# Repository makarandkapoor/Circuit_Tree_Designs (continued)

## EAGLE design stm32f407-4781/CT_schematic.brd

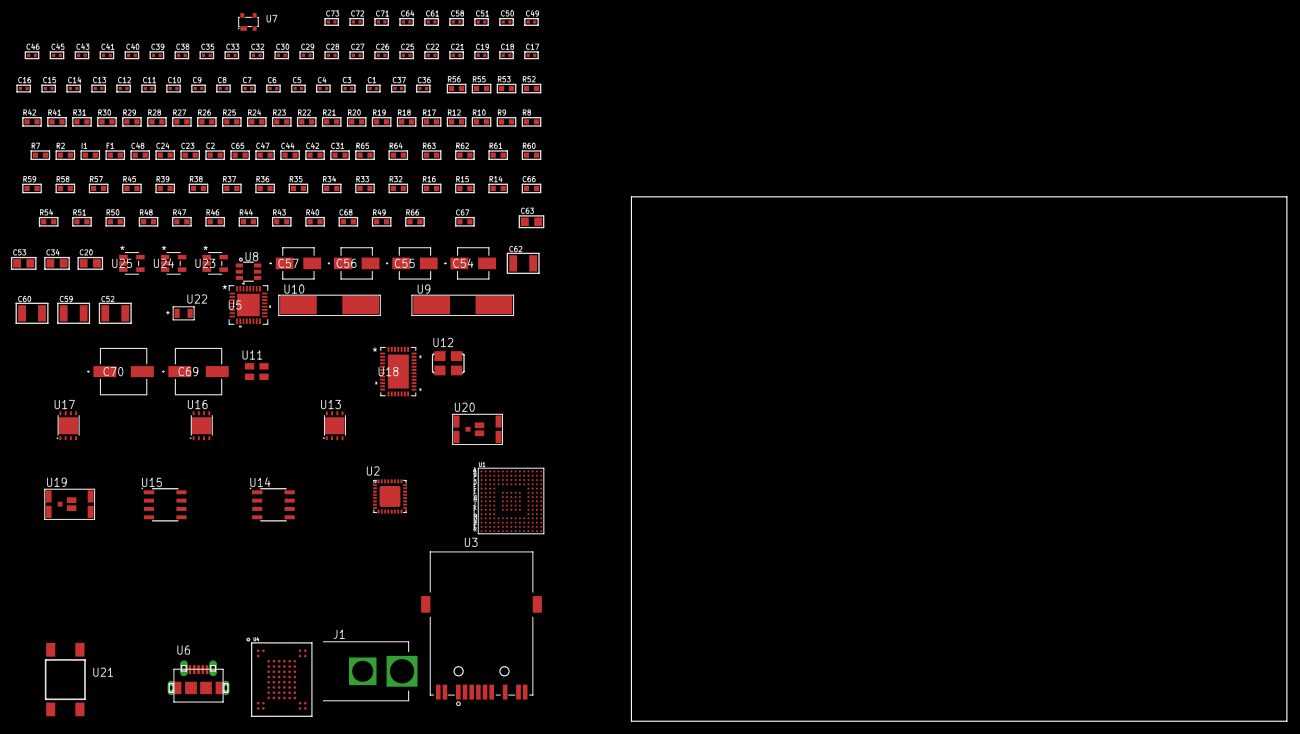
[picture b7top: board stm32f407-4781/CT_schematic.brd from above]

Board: 2 copper layers, 160 parts (0 on the bottom side), 121 nets, no tracks yet.

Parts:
C1, C3, C4, C5, C6, C7, C8, C9, C10, C11, C12, C13, C14, C15, C16, C17, C18, C19, C21, C22, C27, C28, C29, C30, C32, C33, C35, C38, C39, C40, C41, C43, C45, C46, C64: 1e-07; C0402
C2, C24, C48: 1e-06; C0603
C20: 4.7e-06; C0805
C23: 1e-08; C0603
C25, C26: 1e-11; C0402
C31, C42, C44, C47, C65: 2.2e-06; C0603
C34, C53, C63: 1e-05; C0805
C36, C37: 2.2e-11; C0402
C49, C50, C51, C58, C61, C71, C72, C73: 1e-08; C0402
C52, C59, C60, C62: 1e-05; C1210
C54, C56: 1e-06; EXV-9B
C55, C57: 2.2e-06; EXV-9B
C66: 2.45e-08; R0603
C67: 2.8258362168397e-09; R0603
C68: 7.105e-09; R0603
C69, C70: 0.0001; EXV-9H
F1: 600.0; L0603
I1: 97.0; R0603
J1: PJ-037B; PJ-037B_PACKAGE
R2, R24, R25, R26, R28, R29, R30, R42, R53, R56: 1000.0; R0603
R7, R8, R9, R22, R23, R27, R31: 4700.0; R0603
R10, R12: 2200.0; R0603
R14, R15, R16, R32, R33, R34, R35, R36, R38, R39, R57, R59, R60, R63, R64, R65: 10000.0; R0603
R17, R18: 0.1; R0603
R19, R41, R55: 200.0; R0603
R20: 220.0; R0603
R21: 6490.0; R0603
R37, R45: 47000.0; R0603
R40, R43, R44, R46, R47, R48, R50, R51, R54: 100000.0; R0603
R49: 164658.62; R0603
R52: 3900.0; R0603
R58: 75000.0; R0603
R61, R62: 95300.0; R0603
R66: 130963.63636364; R0603
U1: STM32F407IGH6; UFBGA176
U2: KSZ8081RNBIA-TR; QFN-32
U3: 7498011122R
U4: mt29f4g08abbdah4; VFBGA-63
U5: TUSB1210BRHBR; RHB32_3P45X3P45
U6: 47590-0001; MICRO_USB_AB
U7: prtr5v0u2ax; SOT143B
U8: MAX4995AAUT+T; SOT-23-6
U9, U10: ABLS-25.000MHZ-B2F-T
U11: ASEK-32.768KHz-ECST; ASEK
U12: ASFL1-19.2MHZ-NCS; ASFL1
U13, U16, U17: LP3878SDX-ADJ/NOPB; WSON-8
U14, U15: LP2954AIMX/NOPB; LP2954
U18: LTC2928CUHF#PBF; QFN-38_UHF
U19, U20: IRF8306MTRPbF; IRF8306MTRPBF
U21: 4-1437565-2; SW_4-1437565-2
U22: Q65110A2395; LGM67K-G1J2-24-Z
U23, U24, U25: nc7sz125m5x; NC7SZ125M5X

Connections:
CLK_CRYSTAL_U1_G1: C25.1, U1.G1, U9.1
CLK_CRYSTAL_U1_H1: C26.1, U1.H1, U9.2
CLK_CRYSTAL_U2_8: C36.1, U2.8, U10.2
CLK_CRYSTAL_U2_9: C37.1, U2.9, U10.1
CLK_U1_E1: U1.E1, U11.3
CLK_U5_1: U5.1, U12.3
GND: C1.2, C2.2, C3.2, C4.2, C5.2, C6.2, C7.2, C8.2, C9.2, C10.2, C11.2, C12.2, C13.2, C14.2, C15.2, C16.2, C17.2, C18.2, C19.2, C20.2, C21.2, C22.2, C23.2, C24.2, C25.2, C26.2, C27.2, C28.2, C29.2, C30.2, C31.2, C32.2, C33.2, C34.2, C35.2, C36.2, C37.2, C38.2, C39.2, C40.2, C41.2, C42.2, C43.2, C44.2, C45.2, C46.2, C47.2, C48.2, C49.2, C50.2, C51.2, C52.2, C53.2, C54.2, C55.2, C56.2, C57.2, C58.2, C59.2, C60.2, C61.2, C62.2, C63.2, C64.2, C65.2, C66.2, C67.2, C68.2, C69.2, C70.2, C71.2, C72.2, C73.2, J1.2, R2.2, R15.2, R17.2, R18.2, R21.2, R23.2, R24.2, R25.2, R26.2, R28.2, R29.2, R30.2, R37.2, R39.2, R42.2, R46.2, R50.2, R53.2, R56.2, R58.2, R61.2, R62.2, R63.2, R64.2, R65.2, U1.D5, U1.D7, U1.D8, U1.D9, U1.F2, U1.F6, U1.F7, U1.F8, U1.F9, U1.F10, U1.F12, U1.G2, U1.G6, U1.G7, U1.G8, U1.G9, U1.G10, U1.G12, U1.H6, U1.H7, U1.H8, U1.H9, U1.H10, U1.H12, U1.J6, U1.J7, U1.J8, U1.J9, U1.J10, U1.K6, U1.K7, U1.K8, U1.K9, U1.K10, U1.M1, U1.M8, U1.M9, U1.N1, U2.1, U2.EXP, U3.1, U3.10, U4.C5, U4.F7, U4.K3, U4.K8, U5.33, U6.5, U6.6, U6.7, U6.8, U6.9, U7.1, U8.2, U11.2, U12.2, U13.3, U13.PAD, U14.4, U15.4, U16.3, U16.PAD, U17.3, U17.PAD, U18.8, U18.9, U18.10, U18.12, U18.13, U18.24, U18.25, U18.30, U18.32, U18.39, U22.C, U23.1, U23.3, U24.1, U24.3, U25.1, U25.3
NET_U1_C2: U21.3, U21.4
NET_U1_C5: C1.1, C2.1, C3.1, C23.1, C24.1, U1.C1, U1.C5, U1.C6, U1.C7, U1.C8, U1.C9, U1.F3, U1.G3, U1.G13, U1.H13, U1.J12, U1.J13, U1.K4, U1.N8, U1.N9, U1.N10, U1.R1
NET_U1_D6: R14.1, U1.D6
NET_U1_F13: C28.1, U1.F13
NET_U1_J1: R8.1, U1.J1, U24.4
NET_U1_L4: R16.1, U1.L4
NET_U1_M3: R10.1, U1.M3, U2.12
NET_U1_M6: R15.1, U1.M6
NET_U1_P1: C21.1, C22.1, F1.1, U1.P1
NET_U1_P2: R12.1, U1.P2, U2.11
NET_U2_2: C31.1, C32.1, U2.2
NET_U2_3: C33.1, I1.1, U2.3
NET_U2_10: R21.1, U2.10
NET_U2_13: R24.1, U2.13
NET_U2_14: R25.1, U2.14
NET_U2_19: R23.1, U2.19
NET_U2_20: R29.1, U2.20
NET_U2_21: R22.1, U2.21
NET_U2_28: R27.1, U2.28
NET_U2_29: R28.1, U2.29
NET_U2_31: R30.1, U2.31
NET_U2_32: R7.1, U2.32, U23.4
NET_U3_1: U2.7, U3.1
NET_U3_2: C29.1, U3.2
NET_U3_3: U2.6, U3.3
NET_U3_4: U2.5, U3.4
NET_U3_5: C30.1, U3.5
NET_U3_6: U2.4, U3.6
NET_U3_8: R18.1, U3.8
NET_U3_9: R19.1, U3.9
NET_U3_12: R20.1, U3.12
NET_U3_13: R17.1, U3.13, U3.14
NET_U4_C3: R36.1, U4.C3
NET_U5_11: R38.1, U5.11
NET_U5_12: C47.1, U5.12
NET_U5_14: R39.1, U5.14
NET_U5_20: C44.1, U5.20
NET_U5_27: R9.1, U5.27, U25.4
NET_U6_1: C48.1, U5.22, U6.1, U7.4, U8.1
NET_U6_2: U5.19, U6.2, U7.3
NET_U6_3: U5.18, U6.3, U7.2
NET_U6_4: U5.23, U6.4
NET_U8_3: R37.1, U8.3
NET_U8_4: U5.17, U8.4
NET_U13_1: C51.1, U13.1
NET_U13_6: R41.2, R42.1, U13.6
NET_U13_8: R40.1, U13.8
NET_U14_3: R44.1, U14.3
NET_U14_5: R43.1, U14.5
NET_U14_7: R45.2, R46.1, U14.7
NET_U15_3: R48.1, U15.3
NET_U15_5: R47.1, U15.5
NET_U15_7: R49.2, R50.1, U15.7
NET_U16_1: C58.1, U16.1
NET_U16_6: R52.2, R53.1, U16.6
NET_U16_8: R51.1, U16.8
NET_U17_1: C61.1, U17.1
NET_U17_6: R55.2, R56.1, U17.6
NET_U17_8: R54.1, U17.8
NET_U18_3: R64.1, U18.3
NET_U18_6: R61.1, U18.6
NET_U18_7: R62.1, U18.7
NET_U18_16: R63.1, R66.1, U18.16
NET_U18_18: R60.1, U18.18
NET_U18_19: R59.1, U18.19, U18.20
NET_U18_21: R57.1, R58.1, U18.21, U23.2, U24.2, U25.2
NET_U18_22: C64.1, R57.2, R59.2, R60.2, U18.11, U18.22
NET_U18_26: C67.1, U18.26
NET_U18_27: C66.1, U18.27
NET_U18_28: C68.1, U18.28
NET_U18_38: R65.1, U18.38
NET_U19_3: U18.2, U19.3
NET_U20_3: U18.37, U20.3
NET_U21_1: R2.1, U21.1, U21.2
PROC_ETH_RMII_CRS_DV: U1.R3, U2.18
PROC_ETH_RMII_RX_D0: R31.1, U1.N5, U2.16
PROC_ETH_RMII_RX_D1: R26.1, U1.P5, U2.15
PROC_ETH_RMII_TXD0: U1.A8, U2.24
PROC_ETH_RMII_TXD1: U1.A7, U2.25
PROC_ETH_RMII_TX_EN: U1.B9, U2.23
PROC_FSMC_A16: U1.N14, U4.D5
PROC_FSMC_A17: U1.N13, U4.C4
PROC_FSMC_D0: U1.M14, U4.H4
PROC_FSMC_D1: U1.L14, U4.J4
PROC_FSMC_D2: U1.B12, U4.K4
PROC_FSMC_D3: U1.C12, U4.K5
PROC_FSMC_D4: U1.R8, U4.K6
PROC_FSMC_D5: U1.P8, U4.J7
PROC_FSMC_D6: U1.P9, U4.K7
PROC_FSMC_D7: U1.R9, U4.J8
PROC_FSMC_NCE2: R33.1, U1.A11, U4.C6
PROC_FSMC_NOE: R35.1, U1.D10, U4.D4
PROC_FSMC_NWAIT: R32.1, U1.B11, U4.C8
PROC_FSMC_NWE: R34.1, U1.C11, U4.C7
PROC_OTG_HS_ULPI_CK: U1.P4, U5.26
PROC_OTG_HS_ULPI_D0: U1.R2, U5.3
PROC_OTG_HS_ULPI_D1: U1.R5, U5.4
PROC_OTG_HS_ULPI_D2: U1.R4, U5.5
PROC_OTG_HS_ULPI_D3: U1.R12, U5.6
PROC_OTG_HS_ULPI_D4: U1.R13, U5.7
PROC_OTG_HS_ULPI_D5: U1.P12, U5.9
PROC_OTG_HS_ULPI_D6: U1.P13, U5.10
PROC_OTG_HS_ULPI_D7: U1.A6, U5.13
PROC_OTG_HS_ULPI_DIR: U1.E4, U5.31
PROC_OTG_HS_ULPI_NXT: U1.M5, U5.2
PROC_OTG_HS_ULPI_STP: U1.M2, U5.29
VCC_15V8: C65.1, C69.1, C70.1, J1.1, R66.2, U18.23, U19.1, U19.2, U19.6, U19.7, U20.1, U20.2, U20.6, U20.7
VCC_S1_15V8: C52.1, C54.1, C56.1, C59.1, R40.2, R44.2, R48.2, R51.2, U13.4, U14.8, U15.8, U16.4, U19.4, U19.5
VCC_S2_15V8: C62.1, R54.2, U17.4, U20.4, U20.5
VCC_TIER1_1V2: C27.1, C53.1, R41.1, U1.M10, U13.5
VCC_TIER1_1V8: C4.1, C5.1, C6.1, C7.1, C8.1, C9.1, C10.1, C11.1, C12.1, C13.1, C14.1, C15.1, C16.1, C17.1, C18.1, C19.1, C20.1, C34.1, C35.1, C38.1, C39.1, C40.1, C41.1, C42.1, C45.1, C46.1, C55.1, C71.1, C72.1, C73.1, F1.2, R7.2, R8.2, R9.2, R10.2, R12.2, R14.2, R16.2, R22.2, R27.2, R31.2, R32.2, R33.2, R34.2, R35.2, R36.2, R38.2, R43.2, R45.1, U1.F3, U1.G13, U2.17, U4.D3, U4.G4, U4.H8, U4.J6, U5.28, U5.30, U5.32, U14.1, U23.5, U24.5, U25.5
VCC_TIER1_3V3: C43.1, C49.1, C50.1, C57.1, I1.2, R47.2, R49.1, U5.21, U11.4, U12.4, U15.1
VCC_TIER1_5V0: C60.1, R52.1, U8.5, U16.5
VCC_TIER2_1V2: C63.1, R55.1, U17.5

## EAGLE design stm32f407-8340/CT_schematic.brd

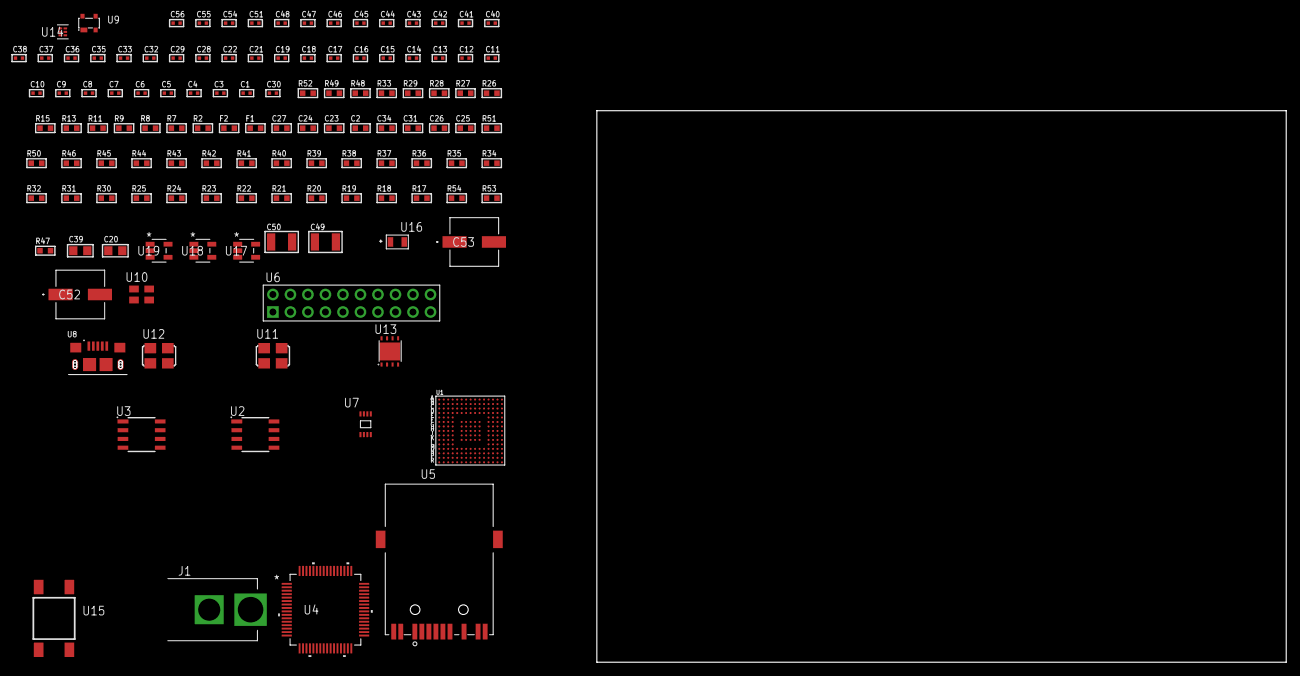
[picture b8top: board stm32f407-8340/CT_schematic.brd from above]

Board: 2 copper layers, 123 parts (0 on the bottom side), 79 nets, no tracks yet.

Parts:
C1, C3, C4, C5, C6, C7, C8, C9, C10, C11, C12, C13, C14, C15, C16, C17, C18, C19, C21, C22, C32, C35, C37, C38, C40, C41, C42, C43, C51: 1e-07; C0402
C2, C24, C27: 1e-06; C0603
C20: 4.7e-06; C0805
C23: 1e-08; C0603
C25, C26, C31, C34: 2.2e-06; C0603
C28, C29, C33, C36, C44, C45, C46, C47, C48, C54, C55, C56: 1e-08; C0402
C30: 1.8e-08; C0402
C39: 1e-05; C0805
C49, C50: 1e-05; C1210
C52, C53: 0.0001; EXV-9H
F1: 600.0; L0603
F2: 510.0; L0603
J1: PJ-037B; PJ-037B_PACKAGE
R2, R49: 1000.0; R0603
R7, R8: 4700.0; R0603
R9, R11, R13, R15: 2200.0; R0603
R17, R18, R19, R20, R21, R22, R23, R24, R25, R30, R31, R32, R34, R35, R36, R37, R38, R39, R40, R41, R42, R43, R44, R45, R46, R50, R51: 10000.0; R0603
R26, R27: 0.1; R0603
R28, R29: 200.0; R0603
R33: 1270.0; R0603
R47: 100000.0; R0603
R48: 2231.0; R0603
R52: 9100.0; R0603
R53: 680000.0; R0603
R54: 120000.0; R0603
U1: STM32F407IGH6; UFBGA176
U2: AT25256B-SSHL-T; SOIC-8
U3: AT25640B-SSHL-T; SOIC-8
U4: BCM5221KPT; TQFP64_10X10MC
U5: 7498011122R
U6: TST-110-05-T-D-RA
U7: 24AA16-I/MC; TDFN-8/6MM
U8: 10118193-0001LF; FCI_10118193-0001LF
U9: prtr5v0u2ax; SOT143B
U10: ASEK-32.768KHz-ECST; ASEK
U11: ASFL1-25MHZ-NCS; ASFL1
U12: ASFL1-50MHZ-NCS; ASFL1
U13: LP3878SDX-ADJ/NOPB; WSON-8
U14: TPS3895ADRYR; SON-6
U15: 4-1437565-2; SW_4-1437565-2
U16: Q65110A2395; LGM67K-G1J2-24-Z
U17, U18, U19: nc7sz125m5x; NC7SZ125M5X

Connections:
CLK_U1_E1: U1.E1, U10.3
CLK_U1_G1: U1.G1, U11.3
CLK_U4_4: U4.4, U12.3
GND: C1.2, C2.2, C3.2, C4.2, C5.2, C6.2, C7.2, C8.2, C9.2, C10.2, C11.2, C12.2, C13.2, C14.2, C15.2, C16.2, C17.2, C18.2, C19.2, C20.2, C21.2, C22.2, C23.2, C24.2, C25.2, C26.2, C27.2, C28.2, C29.2, C30.2, C31.2, C32.2, C33.2, C34.2, C35.2, C36.2, C37.2, C38.2, C39.2, C40.2, C41.2, C42.2, C43.2, C44.2, C45.2, C46.2, C47.2, C48.2, C49.2, C50.2, C51.2, C52.2, C53.2, C54.2, C55.2, C56.2, J1.2, R2.2, R18.2, R19.2, R26.2, R27.2, R30.2, R32.2, R33.2, R34.2, R36.2, R37.2, R38.2, R39.2, R40.2, R46.2, R49.2, R52.2, R54.2, U1.C15, U1.D5, U1.D7, U1.D8, U1.D9, U1.F2, U1.F6, U1.F7, U1.F8, U1.F9, U1.F10, U1.F12, U1.G2, U1.G6, U1.G7, U1.G8, U1.G9, U1.G10, U1.G12, U1.H6, U1.H7, U1.H8, U1.H9, U1.H10, U1.H12, U1.J6, U1.J7, U1.J8, U1.J9, U1.J10, U1.K6, U1.K7, U1.K8, U1.K9, U1.K10, U1.M1, U1.M8, U1.M9, U1.N1, U2.4, U3.4, U4.6, U4.7, U4.24, U4.29, U4.32, U4.40, U4.45, U4.54, U4.63, U5.10, U5.12, U6.4, U6.6, U6.8, U6.10, U6.12, U6.14, U6.16, U6.18, U6.20, U7.4, U8.5, U8.6, U8.7, U8.8, U8.9, U9.1, U10.2, U11.2, U12.2, U13.3, U13.PAD, U14.2, U16.C, U17.2, U17.3, U18.1, U18.3, U19.1, U19.3
NET_U1_B5: R11.1, U1.B5, U7.5
NET_U1_B6: R9.1, U1.B6, U7.6
NET_U1_C2: U15.3, U15.4
NET_U1_C5: C1.1, C2.1, C3.1, C23.1, C24.1, U1.C1, U1.C5, U1.C6, U1.C7, U1.C8, U1.C9, U1.F3, U1.G3, U1.G13, U1.H13, U1.J12, U1.J13, U1.K4, U1.N8, U1.N9, U1.N10, U1.R1
NET_U1_D6: R17.1, U1.D6
NET_U1_F13: C26.1, U1.F13
NET_U1_J1: R8.1, U1.J1, U19.4
NET_U1_L4: R19.1, U1.L4
NET_U1_M3: R13.1, U1.M3, U4.42
NET_U1_M6: R18.1, U1.M6
NET_U1_M10: C25.1, U1.M10
NET_U1_P1: C21.1, C22.1, F1.1, U1.P1
NET_U1_P2: R15.1, U1.P2, U4.41
NET_U2_3: R20.1, U2.3
NET_U2_7: R22.1, U2.7
NET_U3_3: R23.1, U3.3
NET_U3_7: R25.1, U3.7
NET_U4_2: C34.1, C35.1, C36.1, U4.2, U4.55
NET_U4_9: R7.1, U4.9, U18.4
NET_U4_10: R34.1, U4.10
NET_U4_11: R35.1, U4.11
NET_U4_12: R36.1, U4.12
NET_U4_13: R37.1, U4.13
NET_U4_14: R38.1, U4.14
NET_U4_16: R32.1, U4.16
NET_U4_18: R40.1, U4.18
NET_U4_23: R33.1, U4.23
NET_U4_27: C31.1, C32.1, C33.1, U4.22, U4.27, U4.28
NET_U4_37: R39.1, U4.37
NET_U4_38: R30.1, U4.38
NET_U4_39: R31.1, U4.39
NET_U5_1: U4.31, U5.1
NET_U5_2: F2.2, U5.2
NET_U5_3: U4.30, U5.3
NET_U5_4: U4.26, U5.4
NET_U5_5: C30.1, F2.1, U5.2, U5.5
NET_U5_6: U4.25, U5.6
NET_U5_8: R27.1, U5.8
NET_U5_9: R28.1, U5.9
NET_U5_11: R29.1, U5.11
NET_U5_12: R28.2, U5.12
NET_U5_13: R26.1, U5.13, U5.14
NET_U6_19: R46.1, U6.19
NET_U13_1: C48.1, U13.1
NET_U13_6: R48.2, R49.1, U13.6
NET_U13_8: R47.1, U13.8
NET_U14_1: R51.1, R52.1, U14.1
NET_U14_3: R53.2, R54.1, U14.3
NET_U14_4: R50.1, U14.4, U17.4, U18.2, U19.2
NET_U15_1: R2.1, U15.1, U15.2
PROC_ETH_RMII_CRS_DV: U1.R3, U4.62
PROC_ETH_RMII_RX_D0: U1.N5, U4.48
PROC_ETH_RMII_RX_D1: U1.P5, U4.47
PROC_ETH_RMII_TXD0: U1.P12, U4.57
PROC_ETH_RMII_TXD1: U1.P13, U4.58
PROC_ETH_RMII_TX_EN: U1.R13, U4.56
PROC_JTCK_SWCLK: R44.1, U1.A14, U6.9
PROC_JTDI: R42.1, U1.A13, U6.5
PROC_JTDO: U1.A10, U6.13
PROC_JTMS_SWDIO: R43.1, U1.A15, U6.7
PROC_NJTRST: R41.1, U1.A9, U6.3
PROC_OTG_FS_DM: U1.C15, U8.2, U9.3
PROC_OTG_FS_DP: U1.B15, U8.3, U9.2
PROC_OTG_FS_VBUS: C27.1, U1.E15, U8.1, U9.4
PROC_SPI1_MISO: U1.P3, U3.2
PROC_SPI1_MOSI: U1.A6, U3.5
PROC_SPI1_NSS: R24.1, U1.N4, U3.1
PROC_SPI1_SCK: U1.P4, U3.6
PROC_SPI2_MISO: U1.M4, U2.2
PROC_SPI2_MOSI: U1.M5, U2.5
PROC_SPI2_NSS: R21.1, U1.E14, U2.1
PROC_SPI2_SCK: U1.R12, U2.6
RST_OUT_U6_SRESET_B: R45.1, U6.15, U17.1
VCC_S1_14V2: C49.1, C52.1, C53.1, J1.1, R47.2, U13.4
VCC_TIER1_3V3: C4.1, C5.1, C6.1, C7.1, C8.1, C9.1, C10.1, C11.1, C12.1, C13.1, C14.1, C15.1, C16.1, C17.1, C18.1, C19.1, C20.1, C28.1, C29.1, C37.1, C38.1, C39.1, C40.1, C41.1, C42.1, C43.1, C44.1, C45.1, C46.1, C47.1, C50.1, C51.1, C54.1, C55.1, C56.1, F1.2, R7.2, R8.2, R9.2, R11.2, R13.2, R15.2, R17.2, R20.2, R21.2, R22.2, R23.2, R24.2, R25.2, R31.2, R35.2, R41.2, R42.2, R43.2, R44.2, R45.2, R48.1, R50.2, R51.2, R53.1, U1.F3, U1.G13, U2.8, U3.8, U4.1, U4.3, U4.46, U6.1, U6.2, U7.7, U7.8, U10.4, U11.4, U12.4, U13.5, U14.6, U17.5, U18.5, U19.5
